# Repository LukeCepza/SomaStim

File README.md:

### Repository of NeuroSense Somatosensory Stimulation Devices. 
Folders are arranged in Four parts: \
 &nbsp;&nbsp;&nbsp;&nbsp;   1. Electronics Diagrams \
 &nbsp;&nbsp;&nbsp;&nbsp;   2. Firmware \
 &nbsp;&nbsp;&nbsp;&nbsp;   3. Prototypes designs \
 &nbsp;&nbsp;&nbsp;&nbsp;   4. OpenVibe Experiment Modules 

Each of these folders contain subfolders for each module (some may not include a Master Module subfolder): \
 &nbsp;&nbsp;&nbsp;&nbsp;   1. Air \
 &nbsp;&nbsp;&nbsp;&nbsp;   2. Caress \
 &nbsp;&nbsp;&nbsp;&nbsp;   3. Vibration \
 &nbsp;&nbsp;&nbsp;&nbsp;   4. Master 

There is an extra folder with other functions \
Designed by Luke Cepza \
Neurotechs Research Group

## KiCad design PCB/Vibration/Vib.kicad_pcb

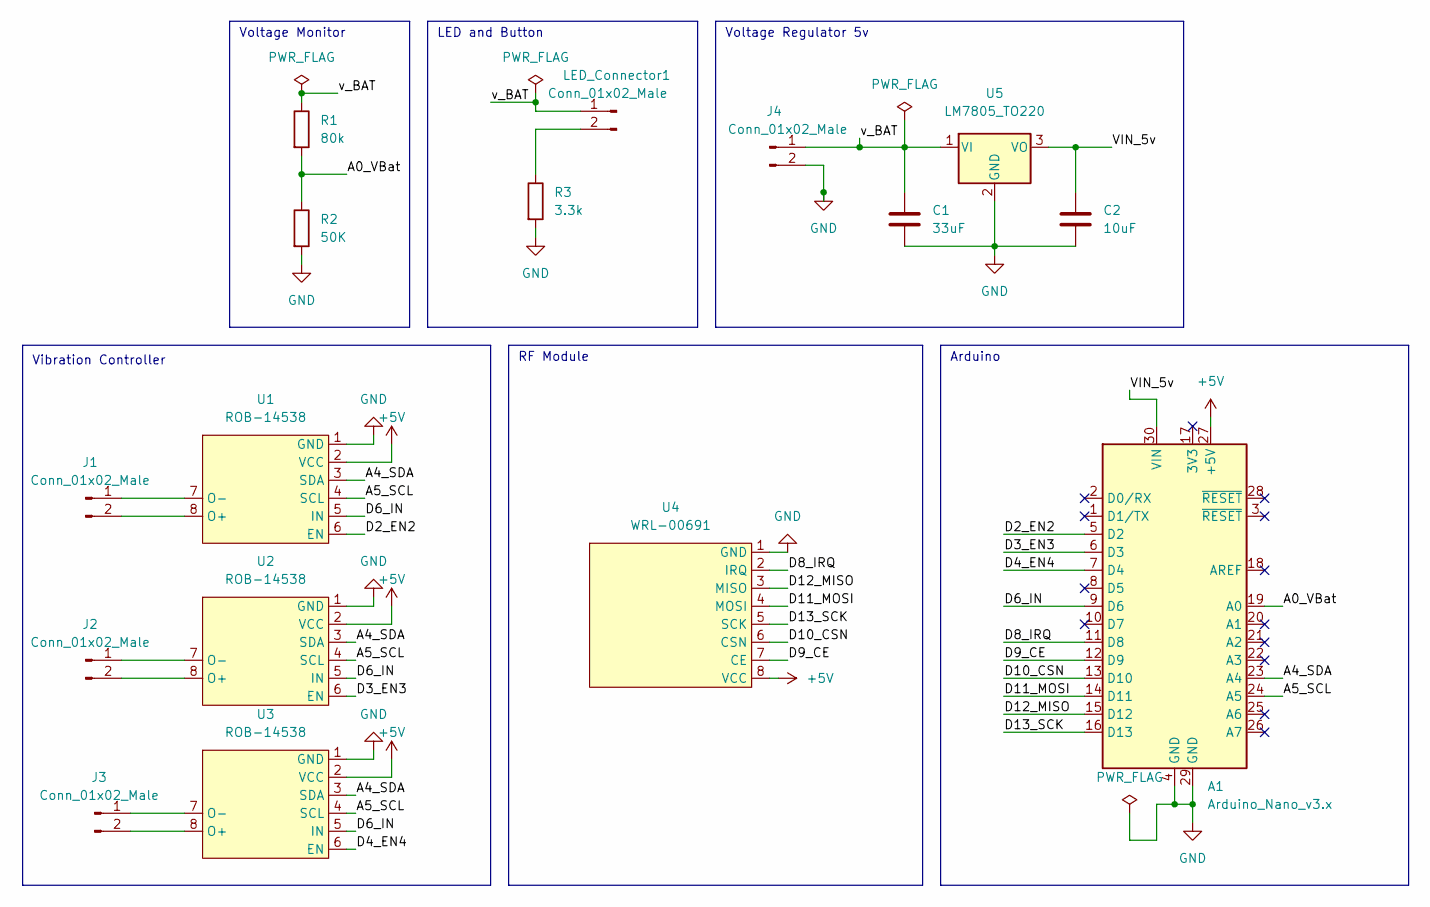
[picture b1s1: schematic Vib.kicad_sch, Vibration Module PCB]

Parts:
A1: Arduino_Nano_v3.x; Arduino_Nano
C1: 33uF; C_Disc_D5.0mm_W2.5mm_P5.00mm
C2: 10uF; C_Disc_D5.0mm_W2.5mm_P5.00mm
J1, J2, J3, J4: Conn_01x02_Male; JST_EH_B2B-EH-A_1x02_P2.50mm_Vertical
LED_Connector1: Conn_01x02_Male; JST_EH_B2B-EH-A_1x02_P2.50mm_Vertical
R1: 80k; R_Axial_DIN0207_L6.3mm_D2.5mm_P7.62mm_Horizontal
R2: 50K; R_Axial_DIN0207_L6.3mm_D2.5mm_P7.62mm_Horizontal
R3: 3.3k; R_Axial_DIN0207_L6.3mm_D2.5mm_P7.62mm_Horizontal
U1, U2, U3: ROB-14538; ROB_14538
U4: WRL-00691
U5: LM7805_TO220; TO-220-3_Vertical

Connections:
+5V: A1.27 (+5V), U1.2 (VCC), U2.2 (VCC), U3.2 (VCC), U4.8 (VCC)
/A0_VBat: A1.19 (A0), R1.2, R2.1
/A4_SDA: A1.23 (A4), U1.3 (SDA), U2.3 (SDA), U3.3 (SDA)
/A5_SCL: A1.24 (A5), U1.4 (SCL), U2.4 (SCL), U3.4 (SCL)
/D2_EN2: A1.5 (D2), U1.6 (EN)
/D3_EN3: A1.6 (D3), U2.6 (EN)
/D4_EN4: A1.7 (D4), U3.6 (EN)
/D6_IN: A1.9 (D6), U1.5 (IN), U2.5 (IN), U3.5 (IN)
/D8_IRQ: A1.11 (D8), U4.2 (IRQ)
/D9_CE: A1.12 (D9), U4.7 (CE)
/D10_CSN: A1.13 (D10), U4.6 (CSN)
/D11_MOSI: A1.14 (D11), U4.4 (MOSI)
/D12_MISO: A1.15 (D12), U4.3 (MISO)
/D13_SCK: A1.16 (D13), U4.5 (SCK)
/VIN_5v: A1.30 (VIN), C2.1, U5.3 (VO)
/v_BAT: C1.1, J4.1, LED_Connector1.1, R1.1, U5.1 (VI); also elsewhere on the board
GND: A1.4 (GND), A1.29 (GND), C1.2, C2.2, J4.2, R2.2, R3.2, U1.1 (GND), U2.1 (GND), U3.1 (GND), U4.1 (GND), U5.2 (GND)
unnamed: J1.1, U1.7 (O-)
unnamed: J1.2, U1.8 (O+)
unnamed: J2.1, U2.7 (O-)
unnamed: J2.2, U2.8 (O+)
unnamed: J3.1, U3.7 (O-)
unnamed: J3.2, U3.8 (O+)
unnamed 23: LED_Connector1.2, R3.1; also elsewhere on the board

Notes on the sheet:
LED and Button
Voltage Regulator 5v
Vibration Controller
RF Module
Arduino
Voltage Monitor

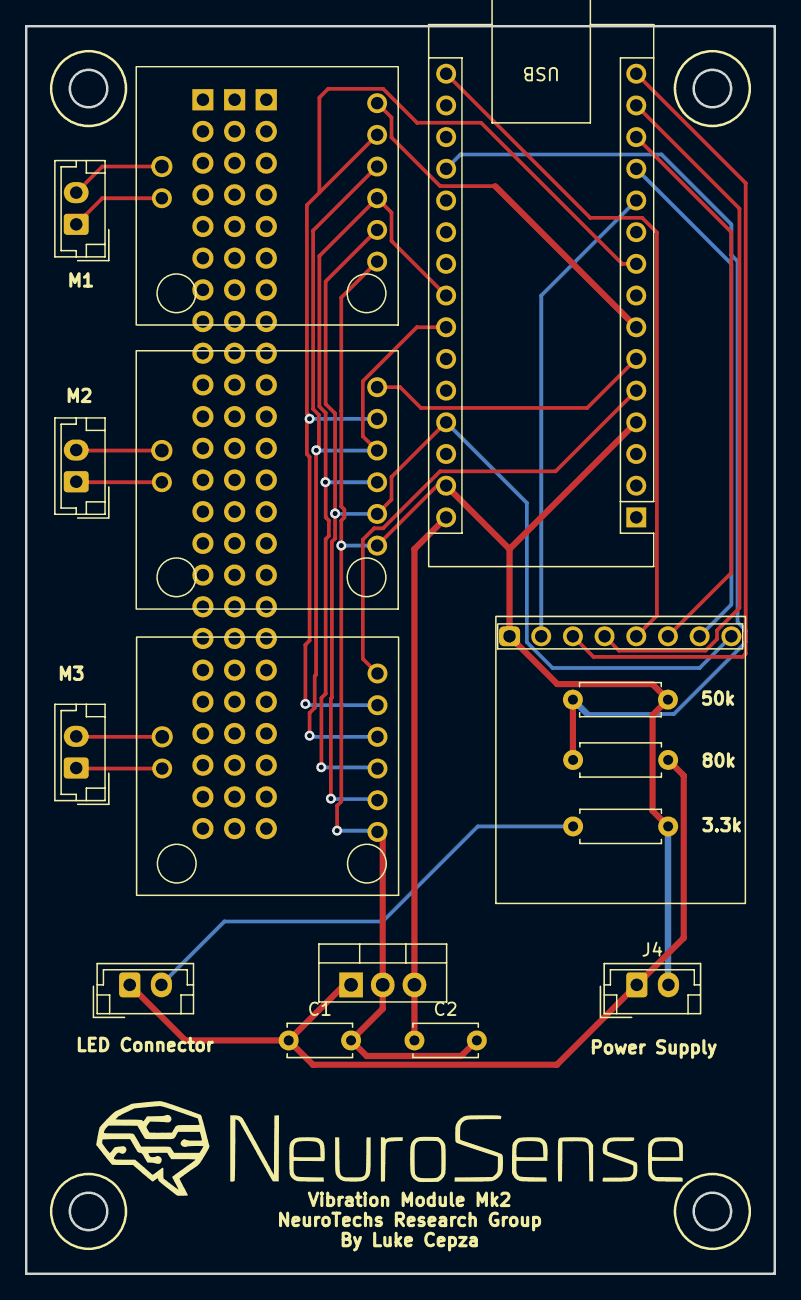
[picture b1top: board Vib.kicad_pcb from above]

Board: 2 copper layers, 60.0 x 100.0 mm, 16 parts (0 on the bottom side), 24 nets.

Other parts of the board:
LED Connector: Conn_01x02_Male; JST_EH_B2B-EH-A_1x02_P2.50mm_Vertical

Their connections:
/v_BAT: LED Connector.1; also elsewhere on the board
unnamed 23: LED Connector.2; also elsewhere on the board

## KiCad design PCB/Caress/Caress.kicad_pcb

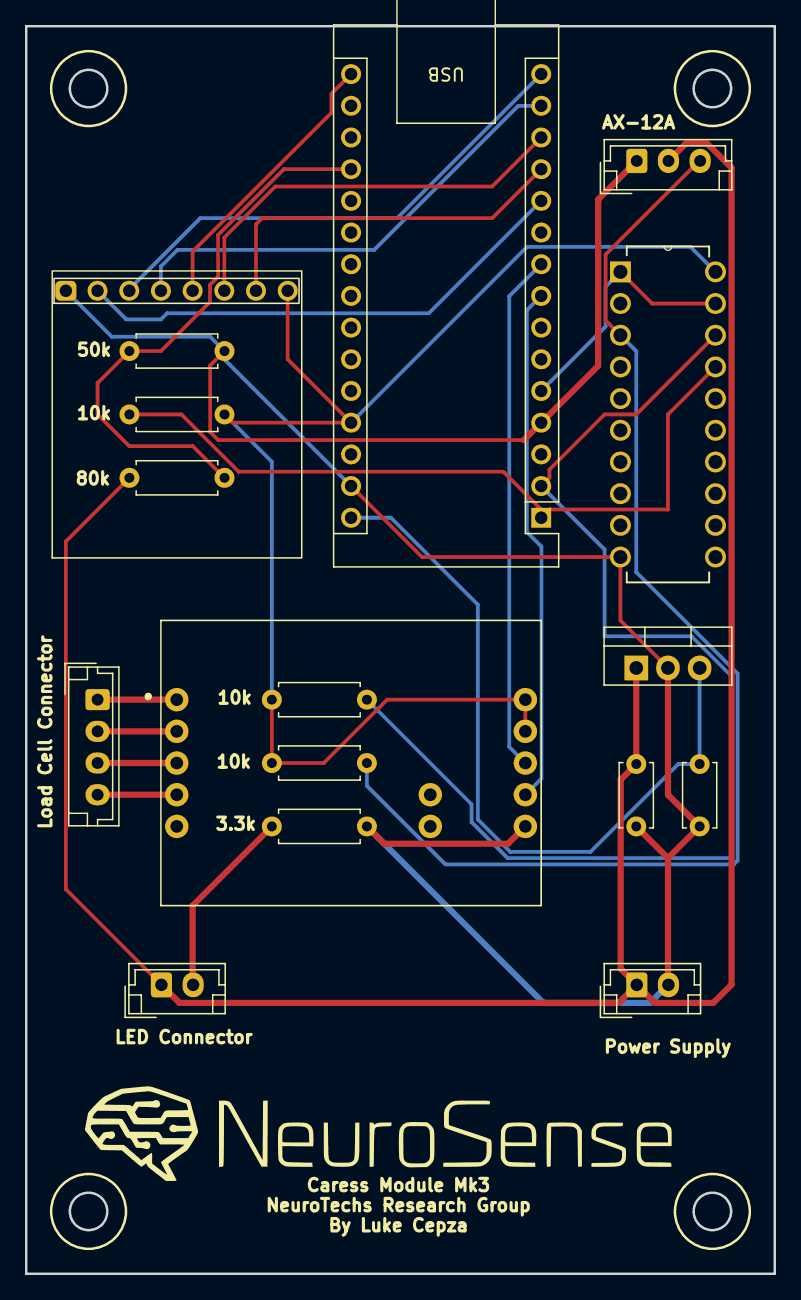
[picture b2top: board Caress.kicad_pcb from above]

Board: 2 copper layers, 60.0 x 100.0 mm, 17 parts (0 on the bottom side), 22 nets.

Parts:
A1: Arduino_Nano_v3.x; Arduino_Nano
C1: 33uF; C_Disc_D5.0mm_W2.5mm_P5.00mm
C2: 10uF; C_Disc_D5.0mm_W2.5mm_P5.00mm
J1: LoadCellConnector; JST_EH_B4B-EH-A_1x04_P2.50mm_Vertical
J2: Conn_01x02_Pin; JST_EH_B2B-EH-A_1x02_P2.50mm_Vertical
J3: Conn_01x02_Male; JST_EH_B2B-EH-A_1x02_P2.50mm_Vertical
J4: Conn_AX12A; JST_EH_B3B-EH-A_1x03_P2.50mm_Vertical
R1: 80k; R_Axial_DIN0207_L6.3mm_D2.5mm_P7.62mm_Horizontal
R2: 50K; R_Axial_DIN0207_L6.3mm_D2.5mm_P7.62mm_Horizontal
R3: 3.3k; R_Axial_DIN0207_L6.3mm_D2.5mm_P7.62mm_Horizontal
R4, R5, R6: 10k; R_Axial_DIN0207_L6.3mm_D2.5mm_P7.62mm_Horizontal
U1: WRL-00691
U2: SEN-13879; SPARKFUN_SEN-13879
U3: LM7805_TO220; TO-220-3_Vertical
U4: SN74LS241N; DIP254P762X508-20

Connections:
+5V: A1.27 (+5V), R4.1, R5.1, R6.1, U1.8 (VCC), U2.9 (VCC), U2.10 (VDD), U4.20 (VCC)
+12V: C1.1, J2.1, J3.1, J4.2, R1.1, U3.1 (VI)
/A0_VBat: A1.19 (A0), R1.2, R2.1
/D0_1Y1: A1.2 (D0/RX), R5.2, U4.18 (1Y1)
/D1_2A4: A1.1 (D1/TX), R4.2, U4.17 (2A4)
/D2_G: A1.5 (D2), U4.1 (1~G), U4.19 (2G)
/D5_CLK: A1.8 (D5), U2.7 (CLK)
/D6_DAT: A1.9 (D6), U2.8 (DAT)
/D8_IRQ: A1.11 (D8), U1.2 (IRQ)
/D9_CE: A1.12 (D9), U1.7 (CE)
/D10_CSN: A1.13 (D10), U1.6 (CSN)
/D11_MOSI: A1.14 (D11), U1.4 (MOSI)
/D12_MISO: A1.15 (D12), U1.3 (MISO)
/D13_SCK: A1.16 (D13), U1.5 (SCK)
/VIN_5v: A1.30 (VIN), C2.1, U3.3 (VO)
GND: A1.4 (GND), A1.29 (GND), C1.2, C2.2, J3.2, J4.1, R2.2, R3.2, U1.1 (GND), U2.6 (GND), U3.2 (GND), U4.10 (GND)
unnamed: J1.1, U2.1 (RED)
unnamed: J1.2, U2.2 (BLK)
unnamed: J1.3, U2.3 (WHT)
unnamed: J1.4, U2.4 (GRN)
unnamed: J2.2, R3.1
unnamed: J4.3, R6.2, U4.3 (2Y4)

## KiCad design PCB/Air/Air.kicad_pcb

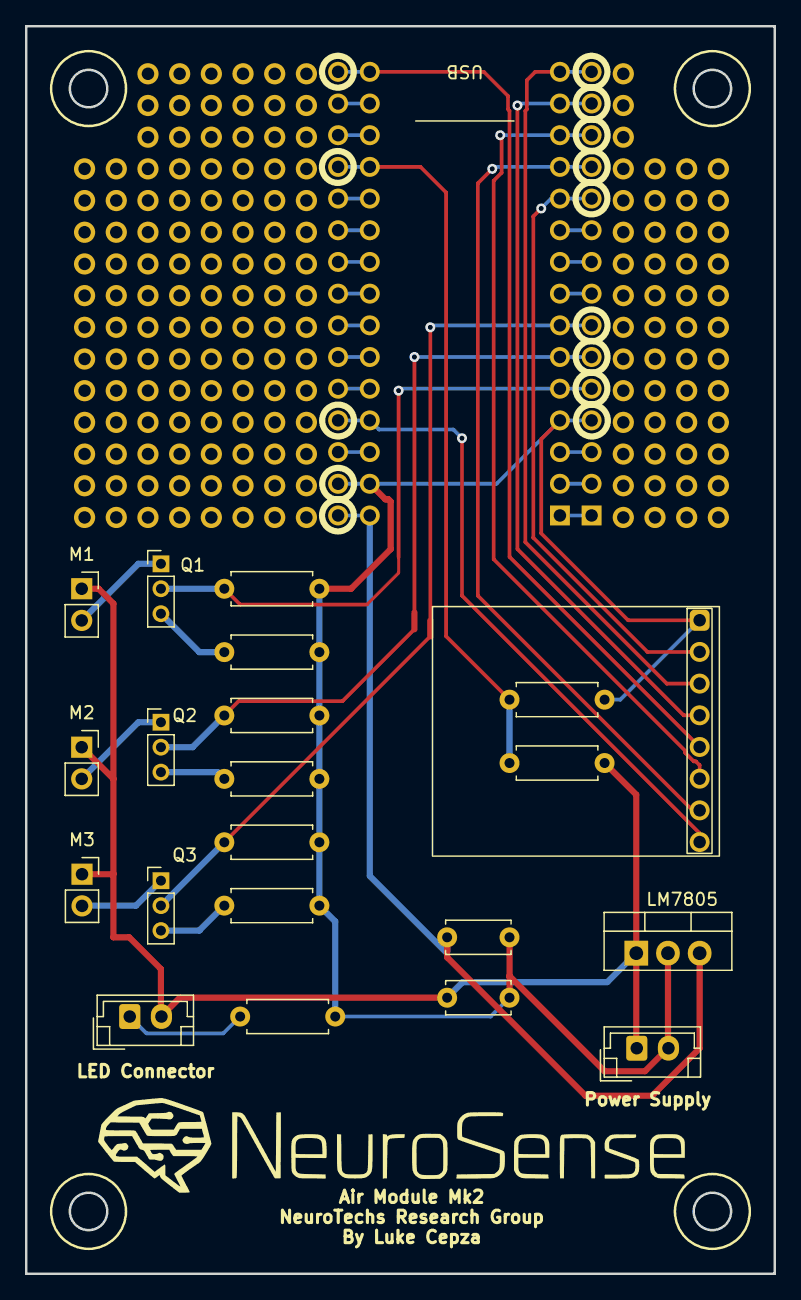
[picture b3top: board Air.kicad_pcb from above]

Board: 2 copper layers, 60.0 x 100.0 mm, 22 parts (0 on the bottom side), 21 nets.

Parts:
A1: Arduino_Nano_v3.x; Arduino_Nano_Connectors side by
C1: 33uF; C_Disc_D5.0mm_W2.5mm_P5.00mm
C2: 10uF; C_Disc_D5.0mm_W2.5mm_P5.00mm
J1: LED; JST_EH_B2B-EH-A_1x02_P2.50mm_Vertical
J2: Battery; JST_EH_B2B-EH-A_1x02_P2.50mm_Vertical
LM7805: LM7805_TO220; TO-220-3_Vertical
M1, M2, M3: Fan; PinSocket_1x02_P2.54mm_Vertical
Q1, Q2, Q3: NPN; PinHeader_1x03_P2.00mm_Vertical
R1, R3, R8: 3.3 k; R_Axial_DIN0207_L6.3mm_D2.5mm_P7.62mm_Horizontal
R2, R7, R9: 100; R_Axial_DIN0207_L6.3mm_D2.5mm_P7.62mm_Horizontal
R4: 80k; R_Axial_DIN0207_L6.3mm_D2.5mm_P7.62mm_Horizontal
R5: 50K; R_Axial_DIN0207_L6.3mm_D2.5mm_P7.62mm_Horizontal
R6: 3.3k; R_Axial_DIN0207_L6.3mm_D2.5mm_P7.62mm_Horizontal
U2: WRL-00691

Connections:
+5V: A1.27 (+5V), U2.8 (VCC)
+12V: C1.1, J1.2, J2.1, LM7805.1 (VI), M1.1 (+), M2.1 (+), M3.1 (+), R4.1
/A0_VBat: A1.19 (A0), R4.2, R5.1
/D2_F1: A1.5 (D2), Q1.2 (B), R1.1
/D3_F2: A1.6 (D3), Q2.2 (B), R3.1
/D4_F3: A1.7 (D4), Q3.2 (B), R8.1
/D8_IRQ: A1.11 (D8), U2.2 (IRQ)
/D9_CE: A1.12 (D9), U2.7 (CE)
/D10_CSN: A1.13 (D10), U2.6 (CSN)
/D11_MOSI: A1.14 (D11), U2.4 (MOSI)
/D12_MISO: A1.15 (D12), U2.3 (MISO)
/D13_SCK: A1.16 (D13), U2.5 (SCK)
/VIN_5v: A1.30 (VIN), C2.1, LM7805.3 (VO)
GND: A1.4 (GND), A1.29 (GND), C1.2, C2.2, J2.2, LM7805.2 (GND), R1.2, R2.2, R3.2, R5.2, R6.2, R7.2, R8.2, R9.2, U2.1 (GND)
unnamed: J1.1, R6.1
unnamed: M1.2 (-), Q1.1 (C)
unnamed: M2.2 (-), Q2.1 (C)
unnamed: M3.2 (-), Q3.1 (C)
unnamed: Q1.3 (E), R2.1
unnamed: Q2.3 (E), R7.1
unnamed: Q3.3 (E), R9.1

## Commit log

2022-02-24 Added Readme
2022-02-24 Added the function to make work python code
2022-02-24 Added versions of code that i have
2022-02-24 Changed ReadMe.md
2022-02-26 Added most recent versions of code and lua
2022-02-26 last version of vibrations
2022-02-26 "ultimas versiones"
2022-03-01 Simplified a few things, may be worth trying
2022-03-01 Updated code labels
2022-03-17 Cambiso para que el tensado se haga desde el master, y el prototipo de caricia ahora funciona con modo servo
2022-03-24 Changes for touch prototipe
2022-03-25 Falta ERP stim, solo esta en tensado
2022-03-28 Updates stim and tense
2022-03-28 Almost FInal version, only need to test the system
2022-05-13 OV Actualizado
2022-05-19 Master_v4.ino
    New label codes for Threshold (33041) and Paro (33042).
    Some messages show in LCD screen were updated.
    Missing: How to send TH and PARO label to two modules?
2022-05-19 Last version worked
    Final version of Vibrations.
    - Threshold calculation ready.
    - PARO label ready.
    - Main function (stimuli) ready.
2022-05-19 Final: Threshold & Paro
    Final version worked of Air Module.
    - Threshold calculation ready.
    - PARO ready.
    - Stimulation process ready.
2022-06-02 Cambiso recientes para conectividad OV > Python > Arduino
2022-06-02 Removed older version
2022-06-02 Adecuación aire para OV > Python > Arduino
2022-06-03 Air now works properly
2022-11-08 20_stimuli
    Se eliminaron las líneas de threshold, se arreglaron las líneas de estímulos dentro de un for que mandará los 20 estímulos.
2022-11-08 Validaction_vibraciones
    Quitar el threshold.
    Solo 20 estímulos en un for.
2022-11-08 Vibracinoes
    Experimento comienza 20s después de Play en OpenViBe.
2022-11-08 Agregue caricias y modifique lua
2022-11-08 Vibration mejorado, No ocupa etiqueta de no-threshold pero puede usar threshold. Depende OV.
2022-11-08 no-threshold
    Se adaptó para funcionar con y sin threshold (probar primero).
2022-11-09 reacomodo
    Re-agrupación de las etiquetas por cada módulo
2022-11-09 Corrección 2 líneas
    2 líneas mal re-acomodadas, arregladas
2022-11-09 Adding validation
    Add a "validation flag" code: 33040 when starting the experiment.
2022-11-10 Vibra-Validation flag
    Se agrega a código Lua y Arduino Vib la etiqueta de Validación de Vib: 33041.
    También se agregó a maste para aire (33044) y vibraciones (33041).
2022-11-10 Error Address
    error en address de la validación de aire corregido
2022-11-10 Hice algunios cambios, ahora se ejecuta desde el prompt y como argumento se pone el puerto. ej. python conection_ov_ino.py COM3
2022-11-10 Small correcyion
2022-11-10 Correcion again
2022-11-10 entre comilla simple
2022-11-10 Da mas info
2022-11-10 Muestra todos los errores
2022-11-10 adding stimulation codes
    add estimulation codes path to the file.
    The path changed as the computer did (Erick's pc)
2022-11-10 Regreso al anterior
    Se regresó a la versión anterior, antes del último cambio
2022-11-11 merge
2022-11-11 Ya funcional
2022-11-11 siuu
2022-11-11 Validación
    Editado para agregar un arreglo de intensidades.
2022-11-12 aire 20st
2022-11-12 touch updated, asi ya jala con el rf nomas que tnga el brazo puesto
2022-11-12 Caricia 20 estimulos
    Se creó un uevo programa de caricia para los 20 estímulos
2022-11-12 Variables
    Se agregaron variables entre otras funciones que faltaban para probar para el de caricia.
    No funcionó. Seguir probando.
2022-11-14 End
    se agregó un END que faltaba.
2022-11-14 Muchos cambios, idk que tanto hice jajajalv
2022-11-14 tiempos
    Aire: modificación tiempos interestímulos
    Caricia: duración de tiempos para mandar etiquetas.
    Vibr: cambio de tiempo de envío de etiqueta de validación de 5 a 15s.
2023-02-24 Version que no necesita LSL; Hace falta probarlo
2023-02-24 Added option to select COM port
2023-04-19 Mejore funcionamiento de openvibe
2023-05-22 microboost
    Se agrega microboost en las 2 primeras fuerzas/vibraciones (menos fuertes).
2023-05-22 Matlab codes
2023-07-19 Added PCB Diagrams
2023-07-19 Changed the folder organization
2023-07-19 Changed some folders and added designs of two prototypes
2023-07-19 Update README.md
    Corrected description
2023-07-19 Update README.md
    More corrections
2023-08-01 Cambios de DCNLaptop
2023-08-01 events .txt
2023-08-02 Fixed folders and added validation data
2023-08-05 Updated PCB files; added desing files for caress and vibration
2023-08-05 Added Vibration ElectroBox files
2023-08-07 EventGenerator
2023-08-22 Corrected ino codes
2023-08-23 Comments
    Erick added comments to all .ino files, .lua files and .py files.
    Kevin: check python file comments.
2023-09-08 Create LICENSE
    Added software license
